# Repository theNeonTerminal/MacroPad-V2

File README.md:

# MacroPad V2

This is an improved version of a <a href=''>Macro Pad</a> I made just some time ago

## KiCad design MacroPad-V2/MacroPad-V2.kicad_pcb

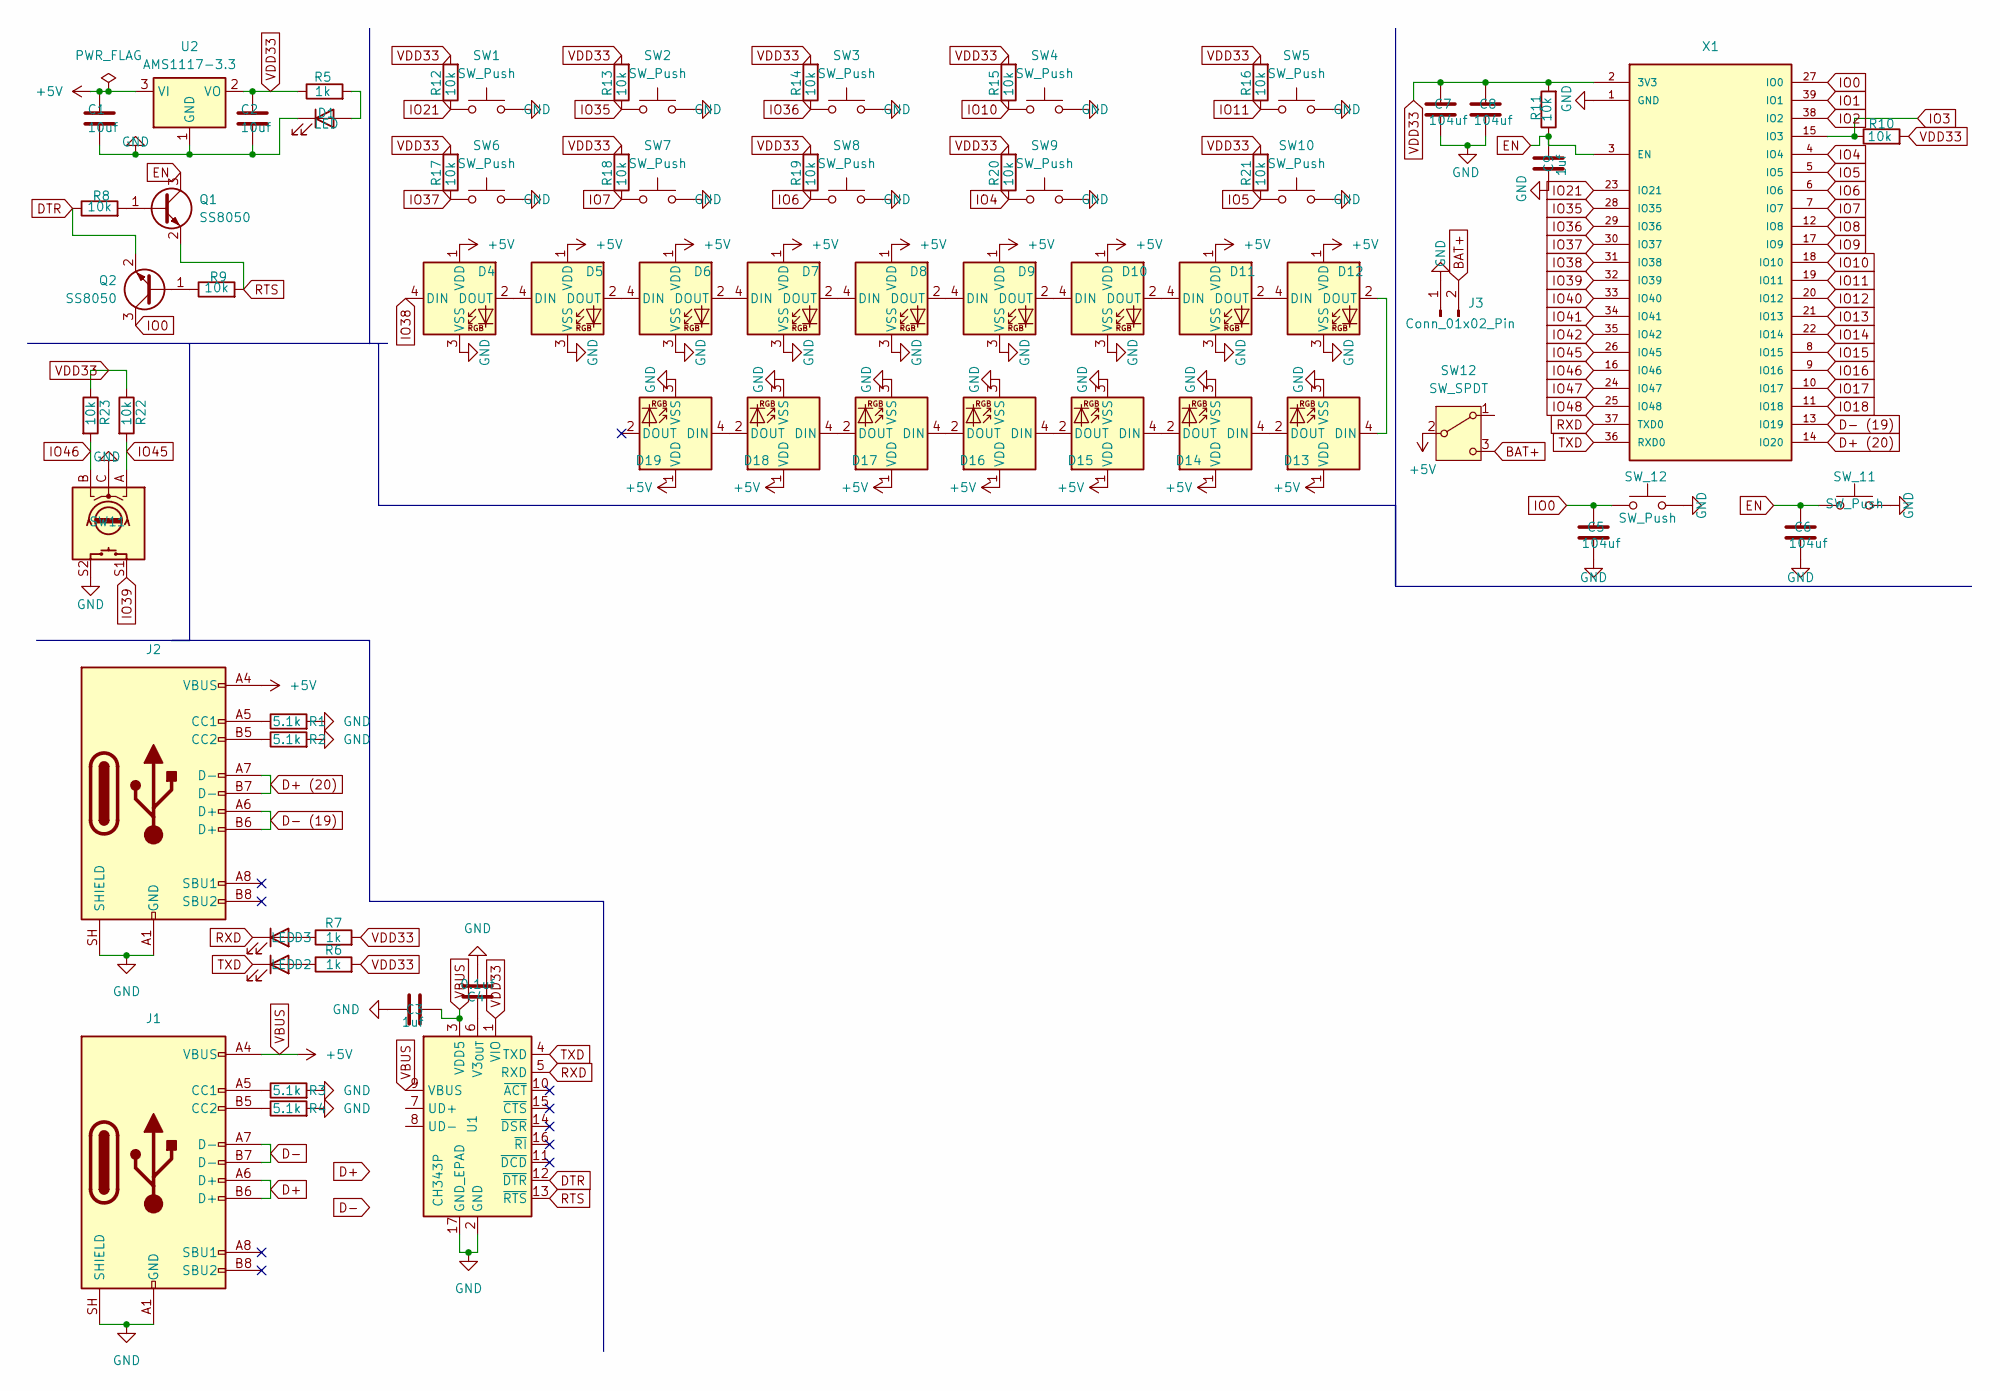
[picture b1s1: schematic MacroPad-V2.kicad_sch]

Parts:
C1, C2: 10uf; C_0603_1608Metric_Pad1.08x0.95mm_HandSolder
C3, C9: 1uf; C_0603_1608Metric_Pad1.08x0.95mm_HandSolder
C4: 0.1uf; C_0603_1608Metric_Pad1.08x0.95mm_HandSolder
C5, C6, C7, C8: 104uf; C_0603_1608Metric_Pad1.08x0.95mm_HandSolder
D1, D2, D3: LED; LED_0603_1608Metric_Pad1.05x0.95mm_HandSolder
D4, D5, D6, D7, D8, D9, D10, D11, D12, D13, D14, D15, D16, D17, D18, D19: WS2812B; LED_WS2812B_PLCC4_5.0x5.0mm_P3.2mm
J1, J2: USB_C_Receptacle_USB2.0_16P; USB_C_Receptacle_GCT_USB4105-xx-A_16P_TopMnt_Horizontal
J3: Conn_01x02_Pin; PinSocket_1x02_P2.54mm_Vertical
Q1, Q2: SS8050; SOT-23
R1, R2, R3, R4: 5.1k; R_0603_1608Metric_Pad0.98x0.95mm_HandSolder
R5, R6, R7: 1k; R_0603_1608Metric_Pad0.98x0.95mm_HandSolder
R8, R9, R10, R11, R12, R13, R14, R15, R16, R17, R18, R19, R20, R21, R22, R23: 10k; R_0603_1608Metric_Pad0.98x0.95mm_HandSolder
SW1, SW2, SW3, SW4, SW5, SW6, SW7, SW8, SW9, SW10: SW_Push; SW_Cherry_MX_PCB_1.00u
SW11: RotaryEncoder_Switch; RotaryEncoder_Alps_EC11E-Switch_Vertical_H20mm
SW12: SW_SPDT; SW_ATE1D-2M3-10-Z
SW_11, SW_12: SW_Push; SW_SPST_CK_RS282G05A3
U1: CH343P; WCH_QFN-16-1EP_3x3mm_P0.5mm_EP1.8x1.8mm
U2: AMS1117-3.3; SOT-223-3_TabPin2
X1: ESP32-S3-WROOM-1-N16R8; ESP32S3WROOM1N8R2; MPN ESP32-S3-WROOM-1-N16R8

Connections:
BAT+: J3.2, SW12.3 (C)
D+: J1.A6 (D+), J1.B6 (D+)
D+ (20): J2.A7 (D-), J2.B7 (D-), X1.14 (IO20)
D-: J1.A7 (D-), J1.B7 (D-)
D- (19): J2.A6 (D+), J2.B6 (D+), X1.13 (IO19)
DTR: Q2.2 (E), R8.1, U1.12 (~DTR)
EN: C6.1, C9.2, Q1.3 (C), R11.1, SW_11.1, X1.3 (EN)
GND: C1.2, C2.2, C3.1, C4.1, C5.2, C6.2, C7.2, C8.2, C9.1, D1.1 (K), D4.3 (VSS), D5.3 (VSS), D6.3 (VSS), D7.3 (VSS), D8.3 (VSS), D9.3 (VSS), D10.3 (VSS), D11.3 (VSS), D12.3 (VSS), D13.3 (VSS), D14.3 (VSS), D15.3 (VSS), D16.3 (VSS), D17.3 (VSS), D18.3 (VSS), D19.3 (VSS), J1.A1 (GND), J1.A12 (GND), J1.B1 (GND), J1.B12 (GND), J1.SH (SHIELD), J2.A1 (GND), J2.A12 (GND), J2.B1 (GND), J2.B12 (GND), J2.SH (SHIELD), J3.1, R1.2, R2.2, R3.2, R4.2, SW1.2, SW2.2, SW3.2, SW4.2, SW5.2, SW6.2, SW7.2, SW8.2, SW9.2, SW10.2, SW11.C, SW11.S2, SW_11.2, SW_12.2, U1.2 (GND), U1.17 (GND_EPAD), U2.1 (GND), X1.1 (GND), X1.40 (GND), X1.41 (GND), X1.42 (GND), X1.43 (GND), X1.44 (GND), X1.45 (GND), X1.46 (GND), X1.47 (GND), X1.48 (GND), X1.49 (GND)
IO0: C5.1, Q2.3 (C), SW_12.1, X1.27 (IO0)
IO1: X1.39 (IO1)
IO2: X1.38 (IO2)
IO3: R10.1, X1.15 (IO3)
IO4: R20.1, SW9.1, X1.4 (IO4)
IO5: R21.1, SW10.1, X1.5 (IO5)
IO6: R19.1, SW8.1, X1.6 (IO6)
IO7: R18.1, SW7.1, X1.7 (IO7)
IO8: X1.12 (IO8)
IO9: X1.17 (IO9)
IO10: R15.1, SW4.1, X1.18 (IO10)
IO11: R16.1, SW5.1, X1.19 (IO11)
IO12: X1.20 (IO12)
IO13: X1.21 (IO13)
IO14: X1.22 (IO14)
IO15: X1.8 (IO15)
IO16: X1.9 (IO16)
IO17: X1.10 (IO17)
IO18: X1.11 (IO18)
IO21: R12.1, SW1.1, X1.23 (IO21)
IO35: R13.1, SW2.1, X1.28 (IO35)
IO36: R14.1, SW3.1, X1.29 (IO36)
IO37: R17.1, SW6.1, X1.30 (IO37)
IO38: D4.4 (DIN), X1.31 (IO38)
IO39: SW11.S1, X1.32 (IO39)
IO40: X1.33 (IO40)
IO41: X1.34 (IO41)
IO42: X1.35 (IO42)
IO45: R22.2, SW11.A, X1.26 (IO45)
IO46: R23.2, SW11.B, X1.16 (IO46)
IO47: X1.24 (IO47)
IO48: X1.25 (IO48)
unnamed: D1.2 (A), R5.2
unnamed: D2.2 (A), R6.1
unnamed: D3.2 (A), R7.1
unnamed: D4.2 (DOUT), D5.4 (DIN)
unnamed: D5.2 (DOUT), D6.4 (DIN)
unnamed: D6.2 (DOUT), D7.4 (DIN)
unnamed: D7.2 (DOUT), D8.4 (DIN)
unnamed: D8.2 (DOUT), D9.4 (DIN)
unnamed: D9.2 (DOUT), D10.4 (DIN)
unnamed: D10.2 (DOUT), D11.4 (DIN)
unnamed: D11.2 (DOUT), D12.4 (DIN)
unnamed: D12.2 (DOUT), D13.4 (DIN)
unnamed: D13.2 (DOUT), D14.4 (DIN)
unnamed: D14.2 (DOUT), D15.4 (DIN)
unnamed: D15.2 (DOUT), D16.4 (DIN)
unnamed: D16.2 (DOUT), D17.4 (DIN)
unnamed: D17.2 (DOUT), D18.4 (DIN)
unnamed: D18.2 (DOUT), D19.4 (DIN)
unnamed: J1.A5 (CC1), R3.1
unnamed: J1.B5 (CC2), R4.1
unnamed: J2.A5 (CC1), R1.1
unnamed: J2.B5 (CC2), R2.1
unnamed: Q1.1 (B), R8.2
unnamed: Q2.1 (B), R9.1
unnamed: C4.2, U1.6 (V3_{OUT})
RTS: Q1.2 (E), R9.2, U1.13 (~RTS)
RXD: D3.1 (K), U1.5 (RXD), X1.37 (TXD0)
TXD: D2.1 (K), U1.4 (TXD), X1.36 (RXD0)
VBUS: C1.1, C3.2, D4.1 (VDD), D5.1 (VDD), D6.1 (VDD), D7.1 (VDD), D8.1 (VDD), D9.1 (VDD), D10.1 (VDD), D11.1 (VDD), D12.1 (VDD), D13.1 (VDD), D14.1 (VDD), D15.1 (VDD), D16.1 (VDD), D17.1 (VDD), D18.1 (VDD), D19.1 (VDD), J1.A4 (VBUS), J1.A9 (VBUS), J1.B4 (VBUS), J1.B9 (VBUS), J2.A4 (VBUS), J2.A9 (VBUS), J2.B4 (VBUS), J2.B9 (VBUS), SW12.2 (B), U1.3 (VDD5), U1.9 (VBUS), U2.3 (VI)
VDD33: C2.1, C7.1, C8.1, R5.1, R6.2, R7.2, R10.2, R11.2, R12.2, R13.2, R14.2, R15.2, R16.2, R17.2, R18.2, R19.2, R20.2, R21.2, R22.1, R23.1, U1.1 (VIO), U2.2 (VO), X1.2 (3V3)

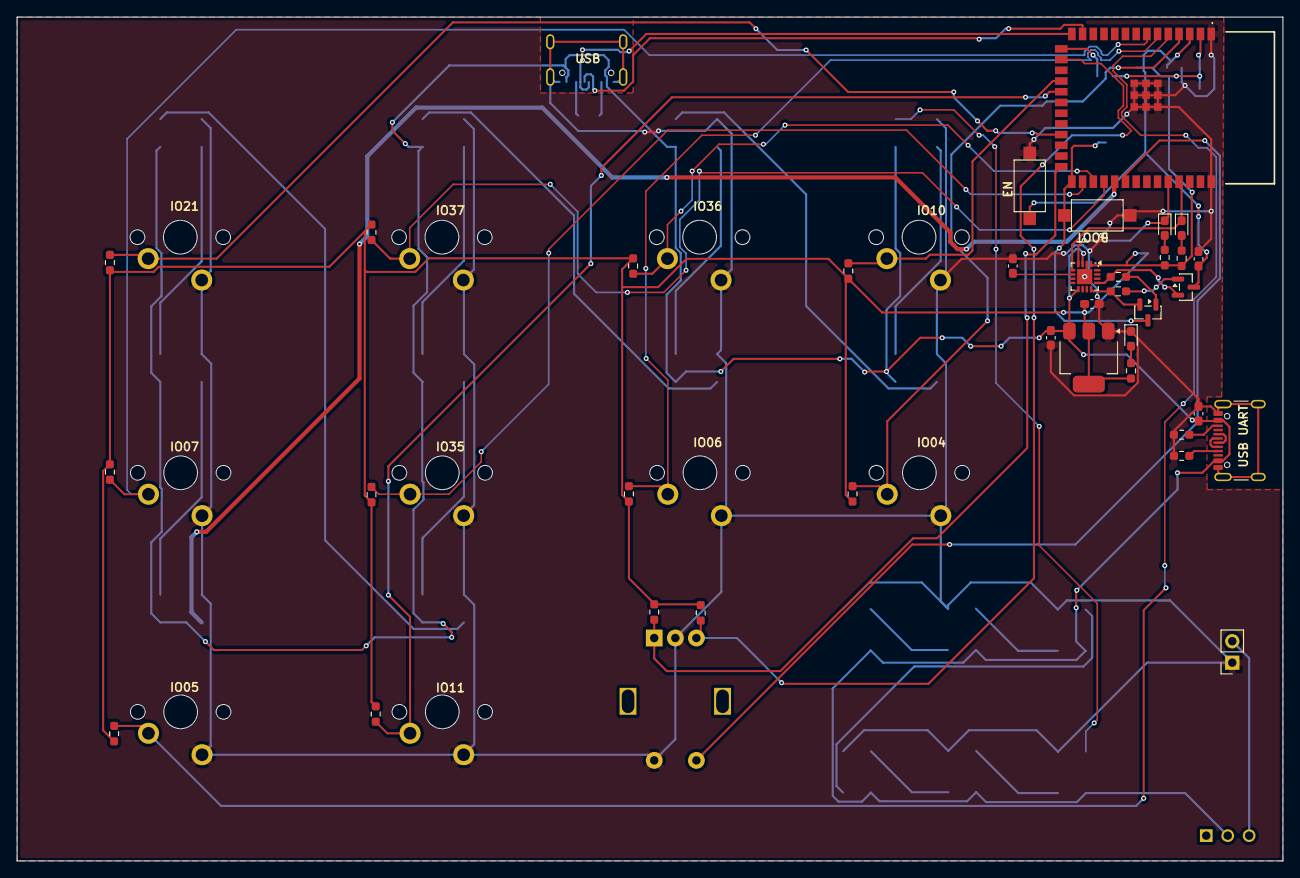
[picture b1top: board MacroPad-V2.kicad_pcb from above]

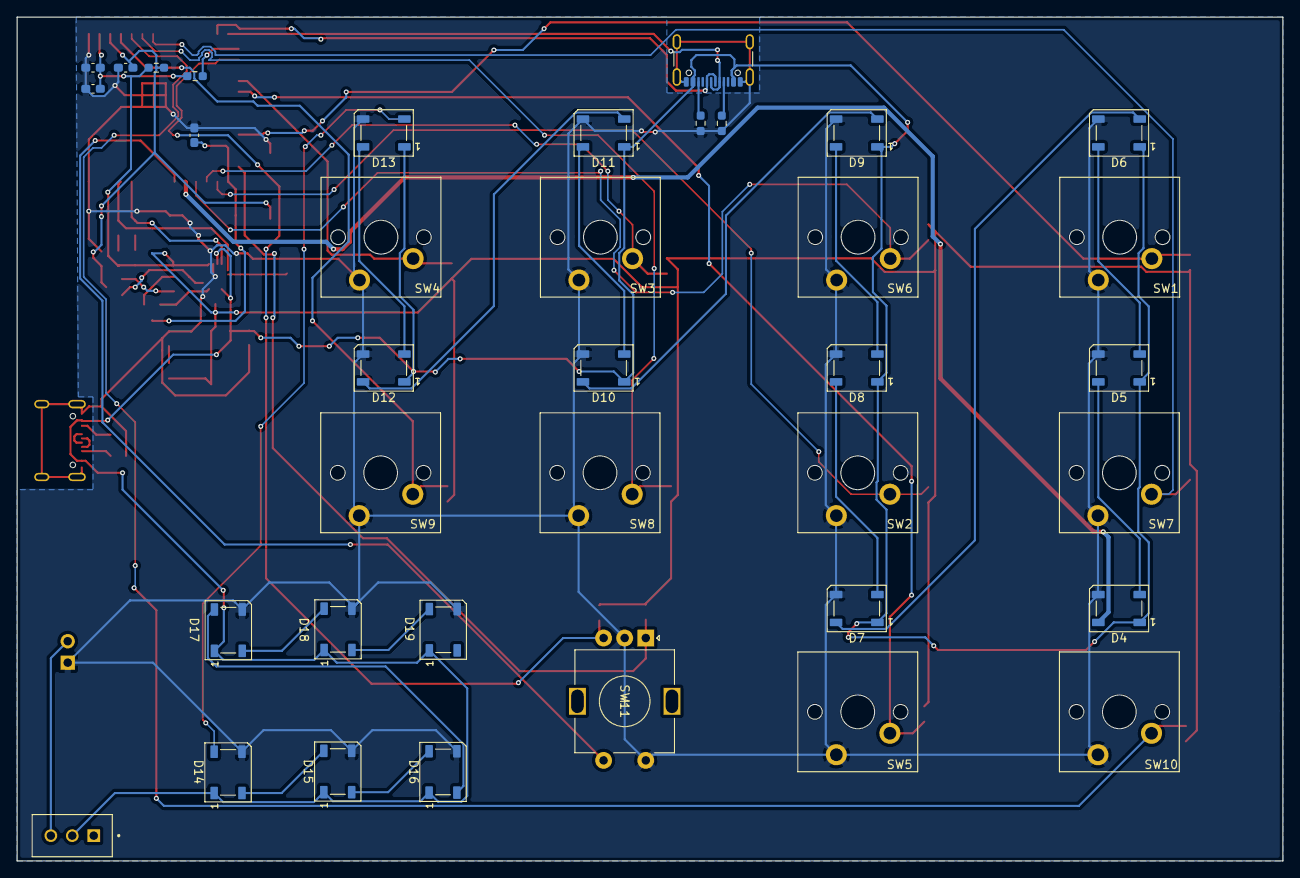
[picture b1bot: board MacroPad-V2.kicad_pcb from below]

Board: 2 copper layers, 150.0 x 100.0 mm, 73 parts (37 on the bottom side), 54 nets.
